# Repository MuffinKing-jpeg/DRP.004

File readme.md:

# DRP.004

Quack with the **new level**!

## Docs

- [Interactive BOM](./Docs/ibom.html)
- [Schematics](./Docs/DRP.004.pdf)
- [Production files](./production/)

## Changes in v3

- Completely new power design
  - 1.8v for MCU + LDR
  - ~5.5v for servo only
- Interface moved to one side.
- MOAR SILK!
- ENIG

## Changes in v4.2

- Switches moved to SMT parts
- Moved USB to same side as other user interfaces
- Changed battery connector to PH2.0
- Changed NTC thermistor to 0402
- Rerouted almost everything

## Changes in v4.3

- Threw to trash few useless resistors  
- Removed power-on by button
- Squished PCB to 27*42mm size  
- Fresh docs

## Changes in v4.4

- CI/CD
- TPS61022 -> TPS63020

## Issues to overcome

- [] Please works as v3

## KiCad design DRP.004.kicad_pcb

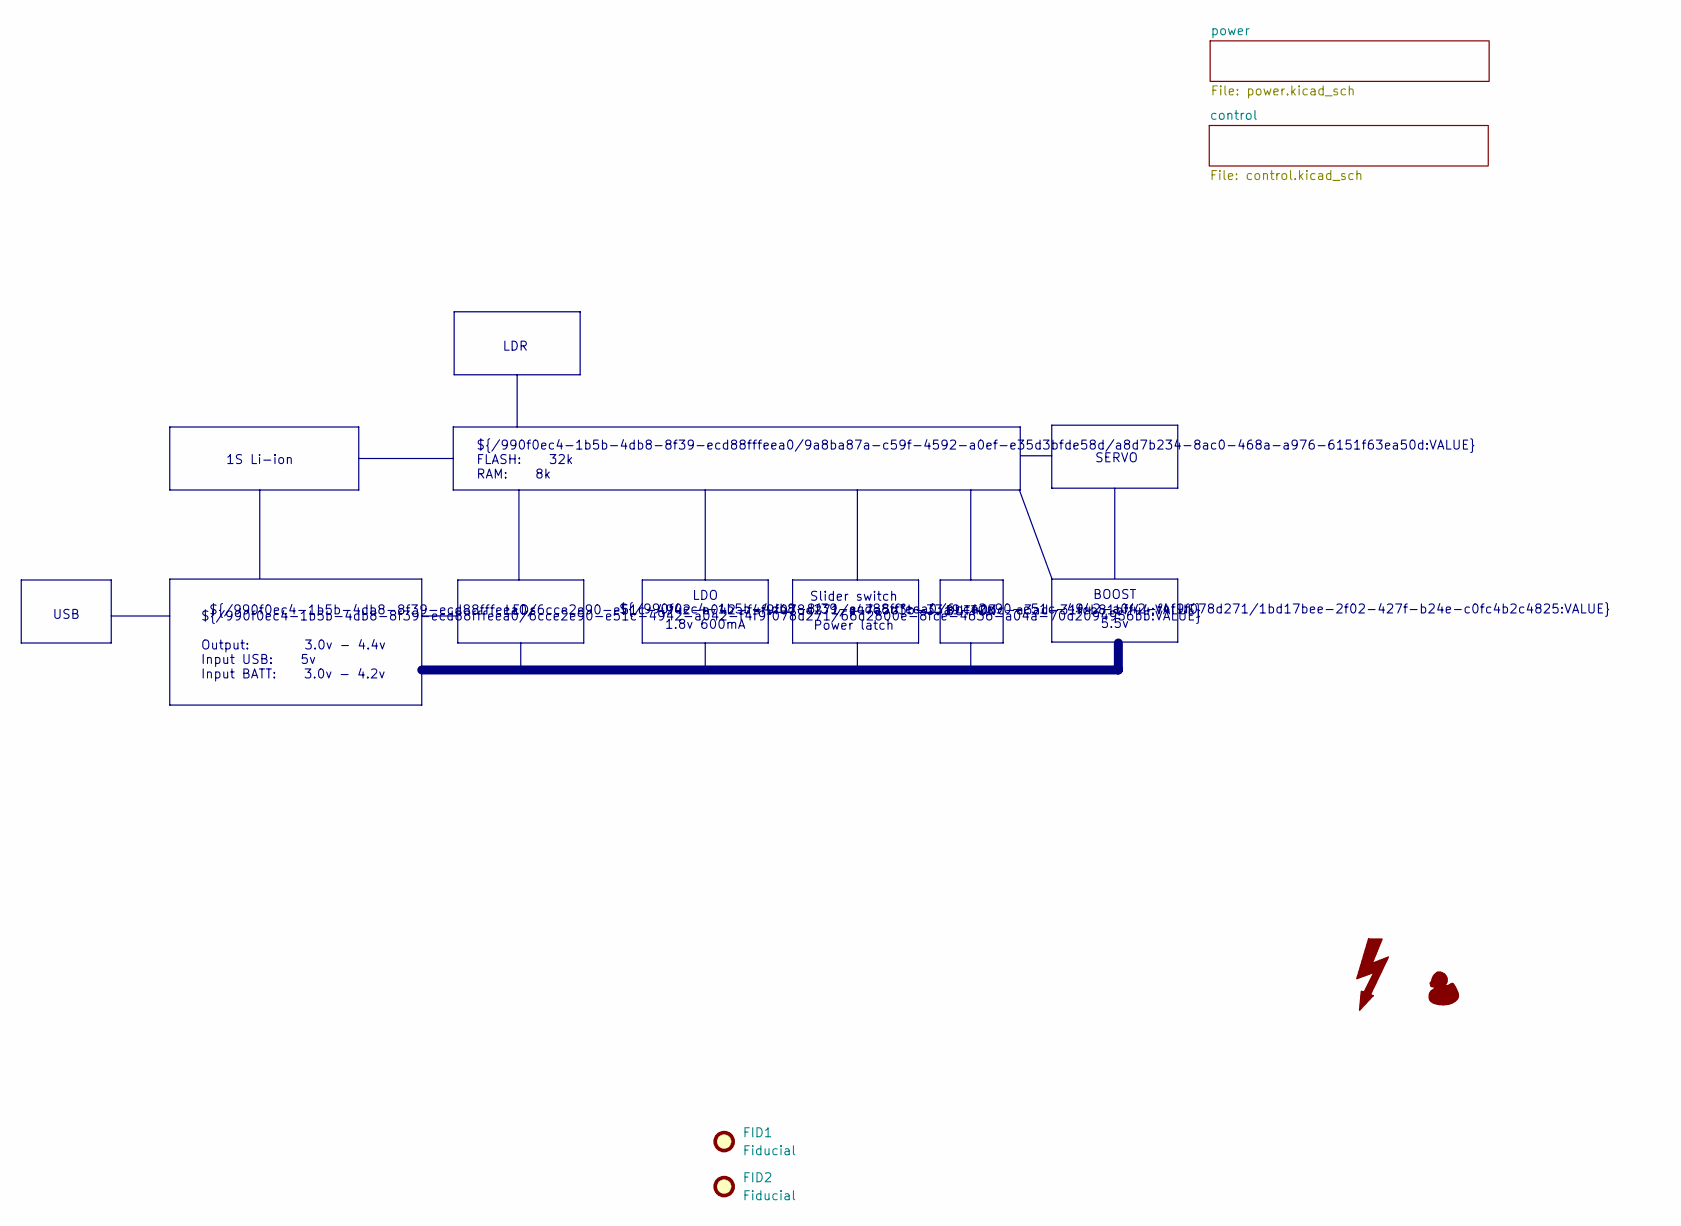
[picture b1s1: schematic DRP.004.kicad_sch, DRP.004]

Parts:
FID1, FID2: Fiducial; Fiducial_0.5mm_Mask1.5mm

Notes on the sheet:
Slider switch + Power latch
LEDs
SERVO
BOOST ${/990f0ec4-1b5b-4db8-8f39-ecd88fffeea0/6cce2e90-e51c-4942-a042-f4f9f078d271/1bd17bee-2f02-427f-b24e-c0fc4b2c4825:VALUE} 5.5v
USB
${/990f0ec4-1b5b-4db8-8f39-ecd88fffeea0/9a8ba87a-c59f-4592-a0ef-e35d3bfde58d/a8d7b234-8ac0-468a-a976-6151f63ea50d:VALUE} FLASH: 32k RAM: 8k
LDO ${/990f0ec4-1b5b-4db8-8f39-ecd88fffeea0/6cce2e90-e51c-4942-a042-f4f9f078d271/c47a5d3b-33a9-403c-a3ad-31fcb81bff44:VALUE} 1.8v 600mA
LDR
${/990f0ec4-1b5b-4db8-8f39-ecd88fffeea0/6cce2e90-e51c-4942-a042-f4f9f078d271/66d2800e-8fce-4636-a04a-70d2094956bb:VALUE} Output: 3.0v - 4.4v Input USB: 5v Input BATT: 3.0v - 4.2v
1S Li-ion
BUTTON

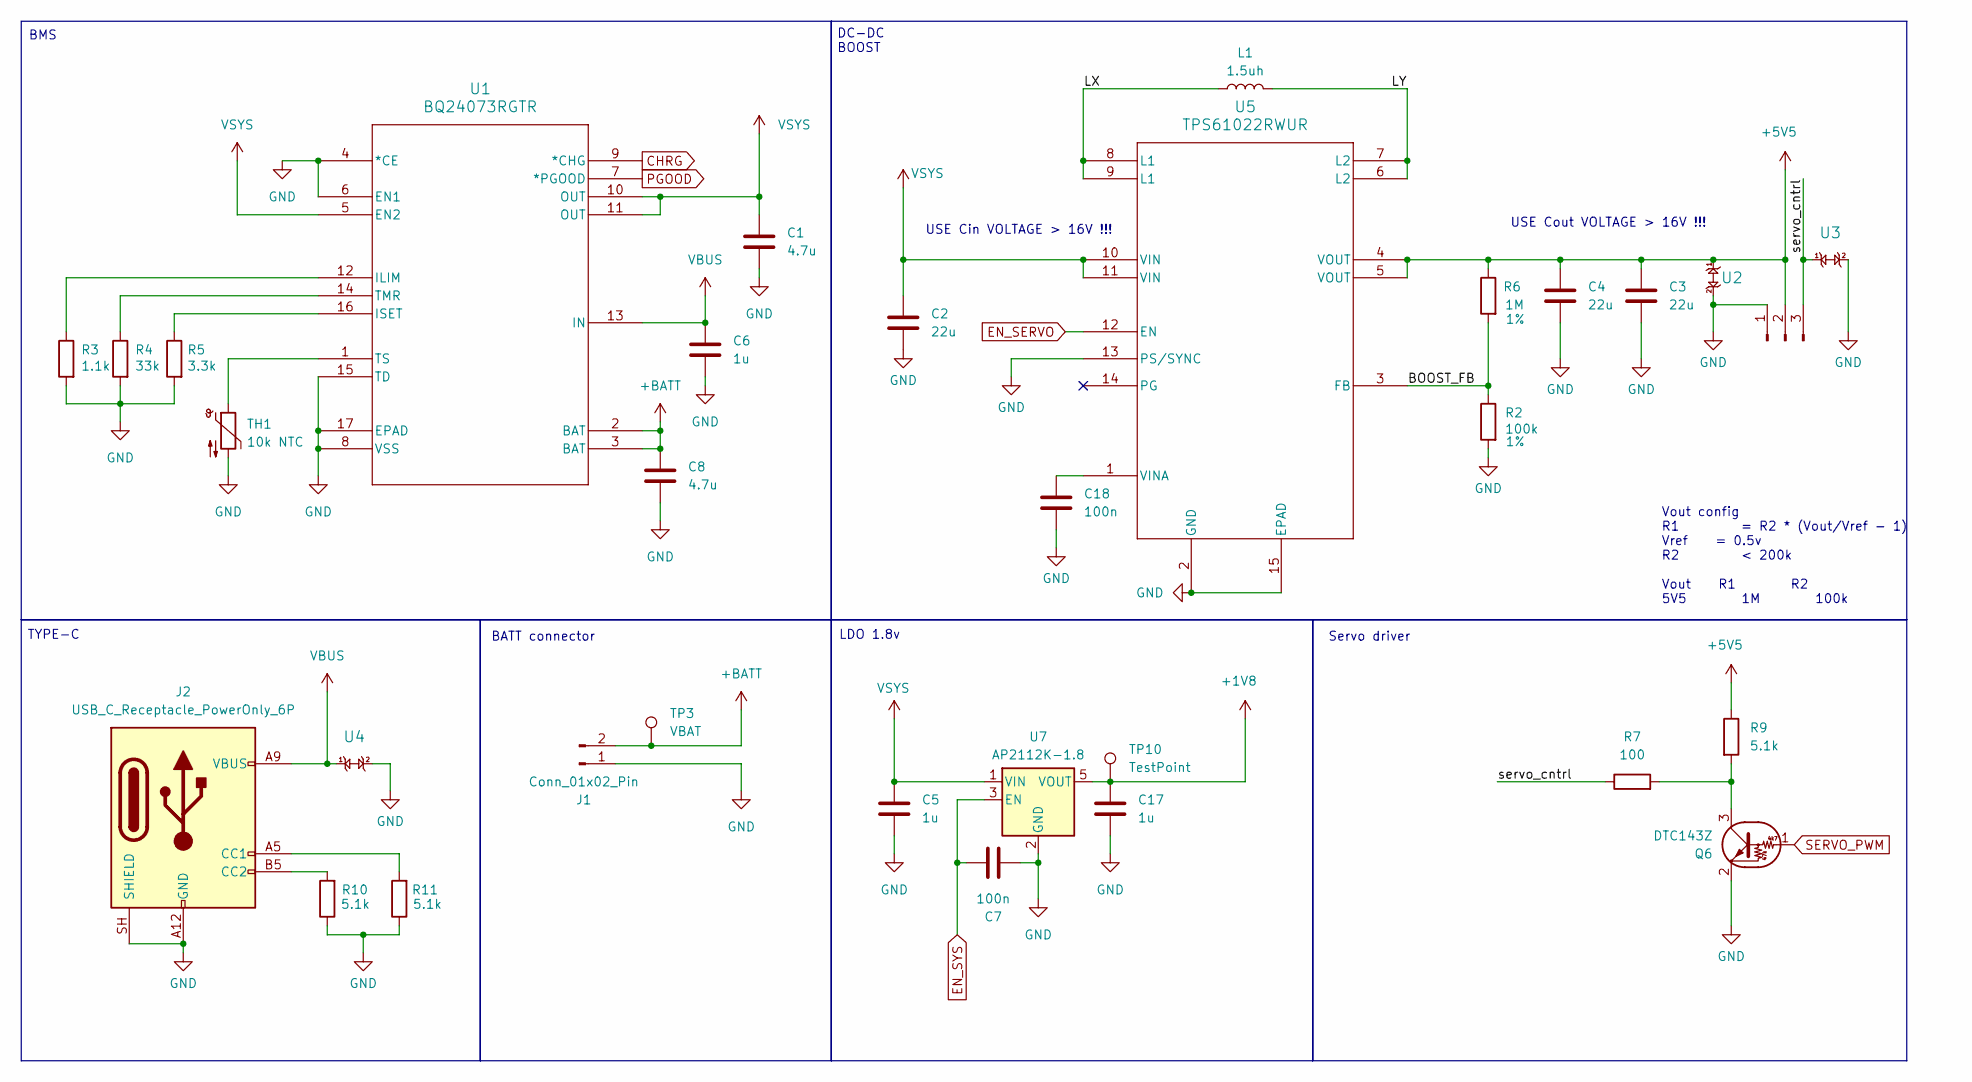
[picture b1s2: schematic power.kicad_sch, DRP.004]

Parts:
C1, C8: 4.7u; C_0603_1608Metric
C2, C3, C4: 22u; C_0805_2012Metric
C5, C6, C17: 1u; C_0603_1608Metric
C7, C18: 100n; C_0603_1608Metric
J1: Conn_01x02_Pin; JST_PH_S2B-PH-K_1x02_P2.00mm_Horizontal
J2: USB_C_Receptacle_PowerOnly_6P; USB_C_Receptacle_GCT_USB4125-xx-x-0190_6P_TopMnt_Horizontal
J3: Conn_01x03_Pin; PinHeader_1x03_P2.54mm_Horizontal
L1: 1.5uh; L_Changjiang_FTC322512S; LCSC C5179444
Q6: DTC143Z; SOT-523; LCSC C2828442
R2: 100k; R_0402_1005Metric; Tolerance 1%
R3: 1.1k; R_0603_1608Metric
R4: 33k; R_0603_1608Metric
R5: 3.3k; R_0603_1608Metric
R6: 1M; R_0402_1005Metric; Tolerance 1%
R7: 100; R_0603_1608Metric
R9, R10, R11: 5.1k; R_0603_1608Metric
TH1: 10k NTC; R_0402_1005Metric
TP3: VBAT; TestPoint_Pad_D1.0mm
TP10: TestPoint; TestPoint_Pad_D1.0mm
U1: BQ24073RGTR; RGT16; LCSC C15220
U2, U3, U4: TPD1E10B06DPYR; X1SON-2_L1.0-W0.6-P0.65-BI; LCSC C48260
U5: TPS61022RWUR; DSJ14_2P85X1P58; LCSC C15483
U7: AP2112K-1.8; SOT-23-5; LCSC C176944

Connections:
+1V8: C17.1, TP10.1 (1_1), U7.5 (VOUT); also elsewhere on the board
+5V5: C3.1, C4.1, J3.2, R6.1, R9.1, U2.1, U5.4 (VOUT), U5.5 (VOUT)
+BATT: C8.1, J1.2, TP3.1 (1_1), U1.2 (BAT), U1.3 (BAT); also elsewhere on the board
/power/BOOST_FB: R2.1, R6.2, U5.3 (FB)
/power/LX: L1.1, U5.8 (L1), U5.9 (L1)
/power/LY: L1.2, U5.6 (L2), U5.7 (L2)
/power/servo_cntrl: J3.3, R7.1, U3.1
CHRG: U1.9 (*CHG); also elsewhere on the board
EN_SERVO: U5.12 (EN); also elsewhere on the board
EN_SYS: C7.2, U7.3 (EN); also elsewhere on the board
GND: C1.2, C2.2, C3.2, C4.2, C5.2, C6.2, C7.1, C8.2, C17.2, C18.2, J1.1, J2.A12 (GND), J2.B12 (GND), J2.SH (SHIELD), J3.1, Q6.2 (E), R2.2, R3.2, R4.2, R5.2, R10.1, R11.1, TH1.2, U1.4 (*CE), U1.6 (EN1), U1.8 (VSS), U1.15 (TD), U1.17 (EPAD), U2.2, U3.2, U4.2, U5.2 (GND), U5.13 (PS/SYNC), U5.15 (EPAD), U7.2 (GND); also elsewhere on the board
unnamed: J2.A5 (CC1), R11.2
unnamed: J2.B5 (CC2), R10.2
unnamed: Q6.3 (C), R7.2, R9.2
unnamed: R3.1, U1.12 (ILIM)
unnamed: R5.1, U1.16 (ISET)
unnamed: R4.1, U1.14 (TMR)
unnamed: TH1.1, U1.1 (TS)
unnamed: C18.1, U5.1 (VINA)
PGOOD: U1.7 (*PGOOD); also elsewhere on the board
SERVO_PWM: Q6.1 (B); also elsewhere on the board
VBUS: C6.1, J2.A9 (VBUS), J2.B9 (VBUS), U1.13 (IN), U4.1
VSYS: C1.1, C2.1, C5.1, U1.5 (EN2), U1.10 (OUT), U1.11 (OUT), U5.10 (VIN), U5.11 (VIN), U7.1 (VIN); also elsewhere on the board

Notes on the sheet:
USE Cout VOLTAGE > 16V !!!
LDO 1.8v
DC-DC BOOST
TYPE-C
Servo driver
USE Cin VOLTAGE > 16V !!!
BMS
BATT connector
Vout config R1 = R2 * (Vout/Vref - 1) Vref = 0.5v R2 < 200k Vout R1 R2 5V5 1M 100k

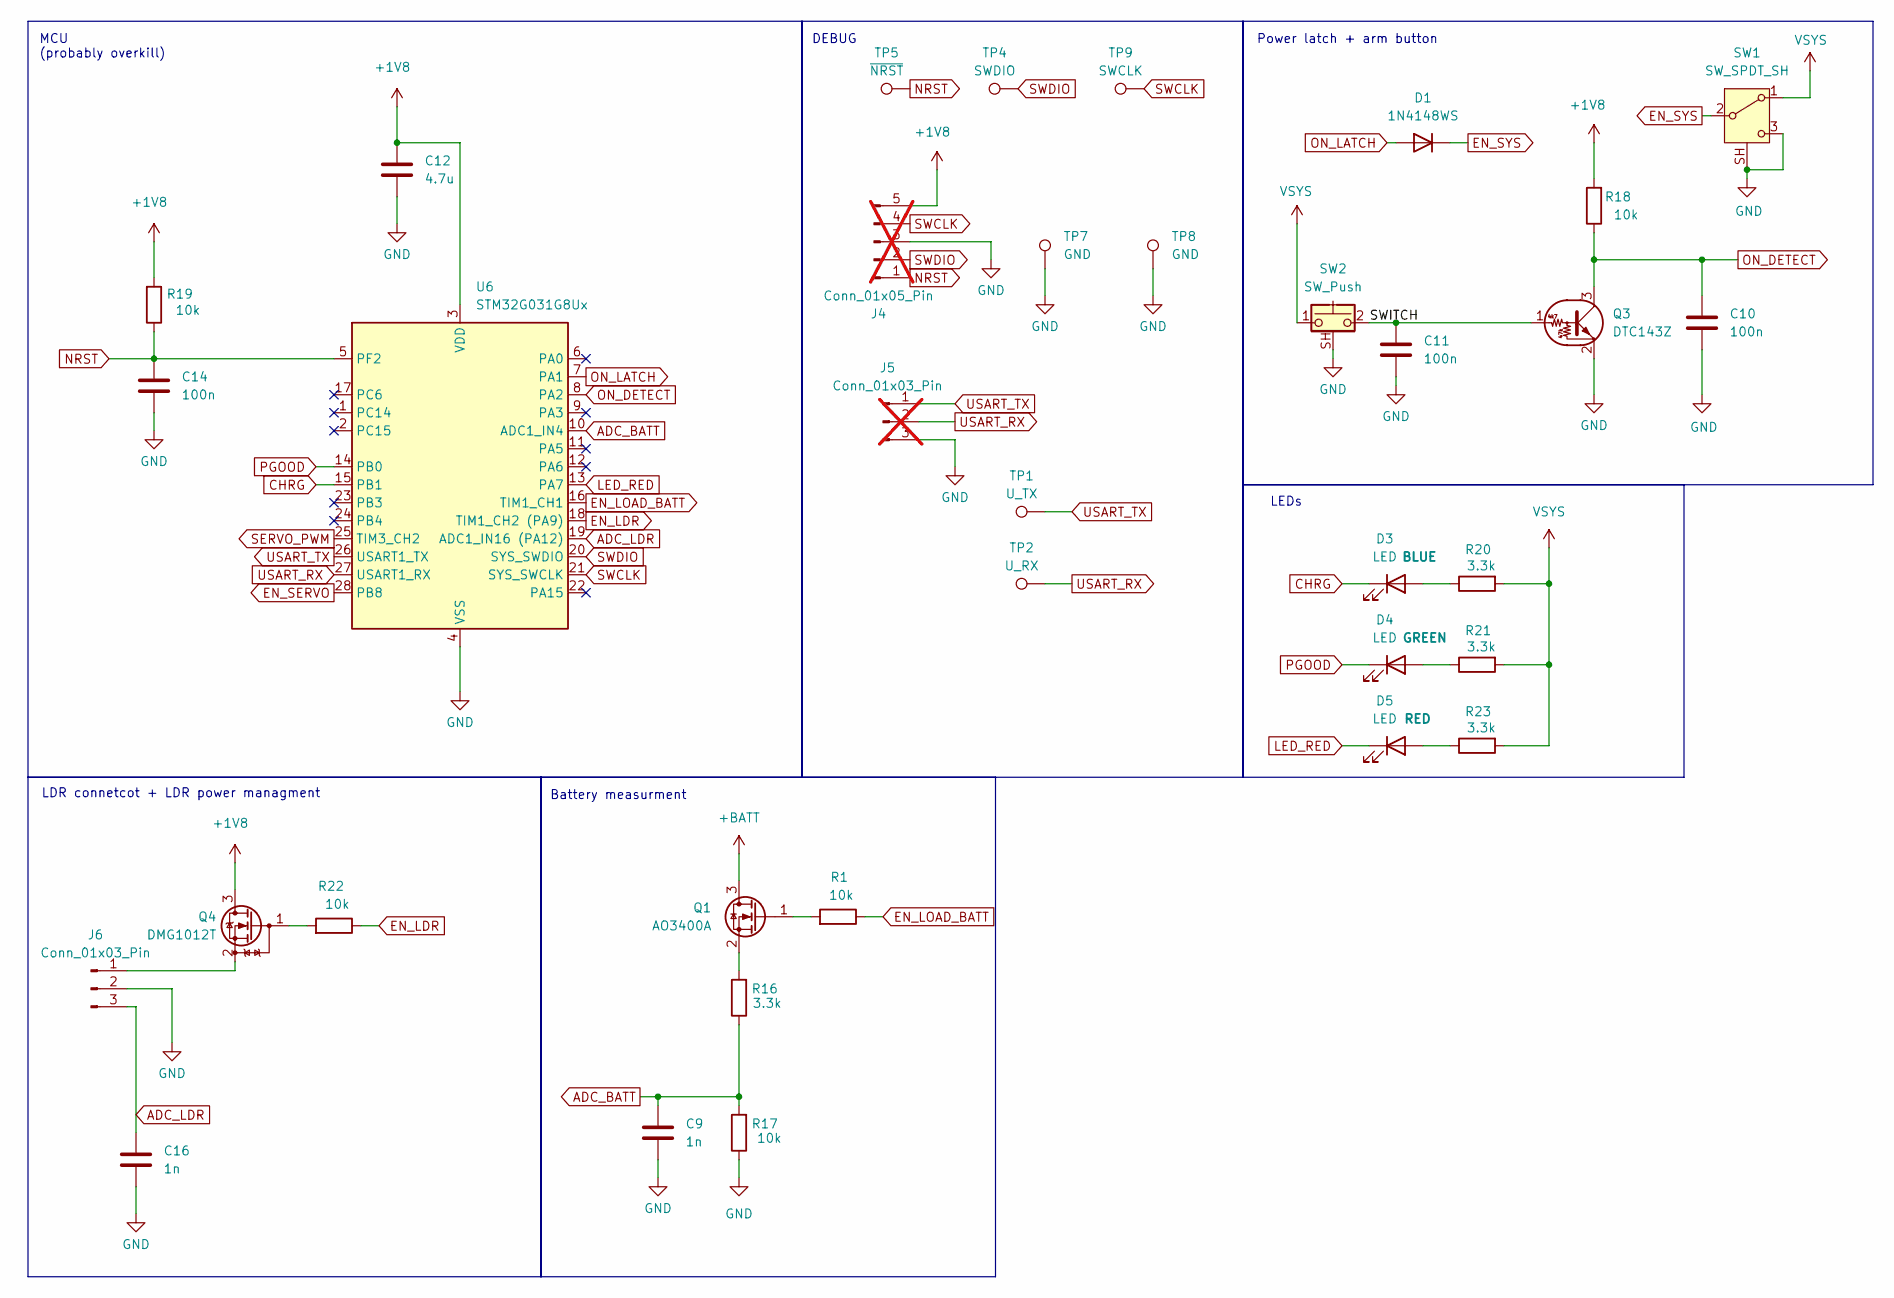
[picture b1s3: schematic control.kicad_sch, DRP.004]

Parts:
C9, C16: 1n; C_0603_1608Metric
C10, C11, C14: 100n; C_0603_1608Metric
C12: 4.7u; C_0603_1608Metric
D1: 1N4148WS; D_SOD-323; LCSC C6423741
D3, D4, D5: LED; LED_0805_2012Metric
J4: Conn_01x05_Pin; Molex_PicoBlade_53048-0510_1x05_P1.25mm_Horizontal; not fitted
J5: Conn_01x03_Pin; Molex_PicoBlade_53048-0310_1x03_P1.25mm_Horizontal; not fitted
J6: Conn_01x03_Pin; Molex_PicoBlade_53048-0310_1x03_P1.25mm_Horizontal
Q1: AO3400A; SOT-23
Q3: DTC143Z; SOT-523; LCSC C2828442
Q4: DMG1012T; SOT-523; LCSC C20512
R1, R17, R18, R19, R22: 10k; R_0603_1608Metric
R16, R20, R21, R23: 3.3k; R_0603_1608Metric
SW1: SW_SPDT_SH; MSK12C02; LCSC C109335
SW2: SW_Push; SW_Push_1P1T-MP_NO_Horizontal_Alps_SKRTLAE010; LCSC C398057
TP1: U_TX; TestPoint_Pad_D1.0mm
TP2: U_RX; TestPoint_Pad_D1.0mm
TP4: SWDIO; TestPoint_Pad_D1.0mm
TP5: ~{NRST}; TestPoint_Pad_D1.0mm
TP7, TP8: GND; TestPoint_Pad_D1.0mm
TP9: SWCLK; TestPoint_Pad_D1.0mm
U6: STM32G031G8Ux; QFN-28_4x4mm_P0.5mm; LCSC C432211

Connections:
+1V8: C12.1, J4.5, Q4.3 (D), R18.2, R19.2, U6.3 (VDD); also elsewhere on the board
+BATT: Q1.3 (D); also elsewhere on the board
/control/SWITCH: C11.1, Q3.1 (B), SW2.2
ADC_BATT: C9.1, R16.1, R17.2, U6.10 (ADC1_IN4)
ADC_LDR: C16.1, J6.3, U6.19 (ADC1_IN16 (PA12))
CHRG: D3.1 (K), U6.15 (PB1); also elsewhere on the board
EN_LDR: R22.1, U6.18 (TIM1_CH2 (PA9))
EN_LOAD_BATT: R1.1, U6.16 (TIM1_CH1)
EN_SERVO: U6.28 (PB8); also elsewhere on the board
EN_SYS: D1.1 (K), SW1.2 (B); also elsewhere on the board
GND: C9.2, C10.2, C11.2, C12.2, C14.2, C16.2, J4.3, J5.3, J6.2, Q3.2 (E), R17.1, SW1.3 (C), SW1.SH (Shield), SW2.SH (B), TP7.1 (1_1), TP8.1 (1_1), U6.4 (VSS); also elsewhere on the board
LED_RED: D5.1 (K), U6.13 (PA7)
NRST: C14.1, J4.1, R19.1, TP5.1 (1_1), U6.5 (PF2)
unnamed: D3.2 (A), R20.1
unnamed: D4.2 (A), R21.1
unnamed: D5.2 (A), R23.1
unnamed: J6.1, Q4.2 (S)
unnamed: Q1.1 (G), R1.2
unnamed: Q1.2 (S), R16.2
unnamed: Q4.1 (G), R22.2
ON_DETECT: C10.1, Q3.3 (C), R18.1, U6.8 (PA2)
ON_LATCH: D1.2 (A), U6.7 (PA1)
PGOOD: D4.1 (K), U6.14 (PB0); also elsewhere on the board
SERVO_PWM: U6.25 (TIM3_CH2); also elsewhere on the board
SWCLK: J4.4, TP9.1 (1_1), U6.21 (SYS_SWCLK)
SWDIO: J4.2, TP4.1 (1_1), U6.20 (SYS_SWDIO)
USART_RX: J5.2, TP2.1 (1_1), U6.27 (USART1_RX)
USART_TX: J5.1, TP1.1 (1_1), U6.26 (USART1_TX)
VSYS: R20.2, R21.2, R23.2, SW1.1 (A), SW2.1; also elsewhere on the board

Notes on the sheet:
MCU (probably overkill)
DEBUG
LEDs
LDR connetcot + LDR power managment
Power latch + arm button
Battery measurment

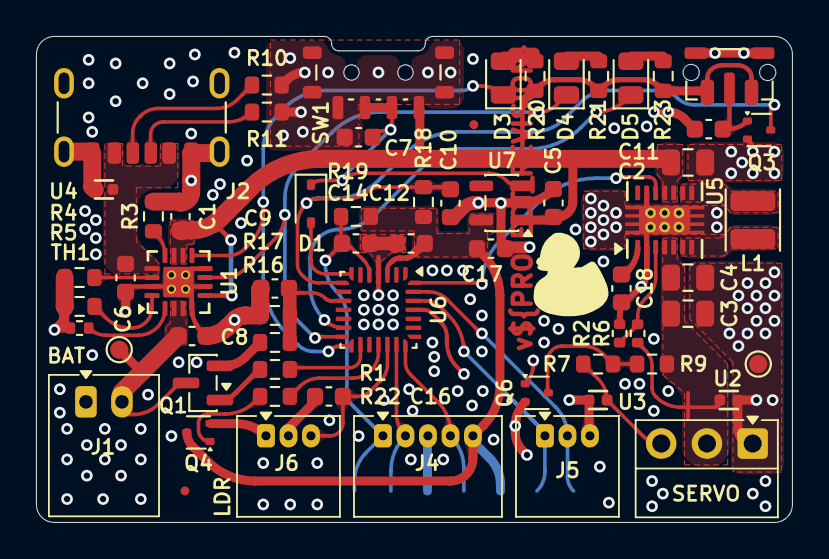
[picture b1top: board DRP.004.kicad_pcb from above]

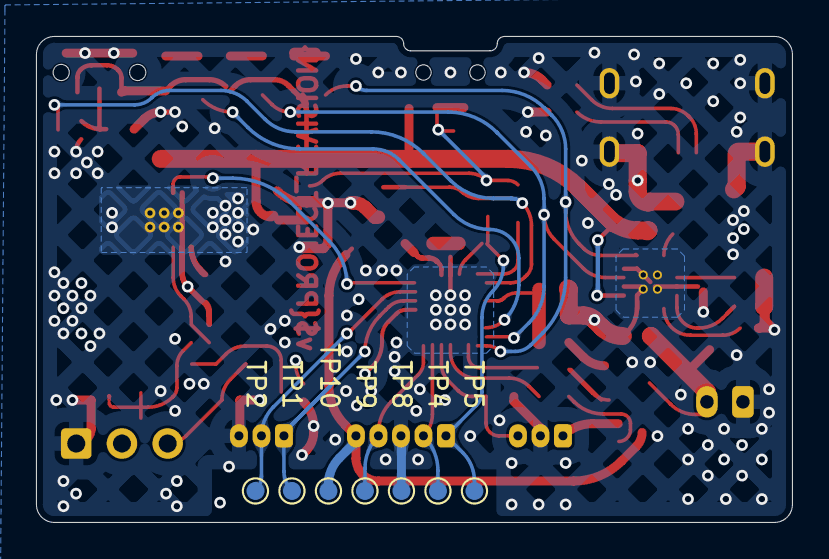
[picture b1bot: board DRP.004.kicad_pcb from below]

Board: 4 copper layers, 42.0 x 27.0 mm, 70 parts (7 on the bottom side), 43 nets.

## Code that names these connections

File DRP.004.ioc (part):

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Mcu.Name=STM32G031G(4-6-8)Ux
Mcu.Package=UFQFPN28
Mcu.UserName=STM32G031G8Ux
PA0.GPIOParameters=GPIO_Label
PA0.GPIO_Label=MODE_SW
PA0.Signal=GPIO_Output
PA1.GPIOParameters=GPIO_Label
PA1.GPIO_Label=LOAD_BATT
PA1.Signal=GPIO_Output
PA11\ [PA9].GPIOParameters=GPIO_Label
PA11\ [PA9].GPIO_Label=PMIC_CHRG
PA11\ [PA9].Signal=GPIO_Input
PA13.Mode=Serial_Wire
PA13.Signal=SYS_SWDIO
PA14-BOOT0.Mode=Serial_Wire
PA14-BOOT0.Signal=SYS_SWCLK
PA2.GPIOParameters=GPIO_Label
PA2.GPIO_Label=ADC_BATT
PA2.Mode=IN2
PA2.Signal=ADC1_IN2
PA3.GPIOParameters=GPIO_Label
PA3.GPIO_Label=ON_LATCH
PA3.Signal=GPIO_Output
PA4.GPIOParameters=GPIO_Label
PA4.GPIO_Label=WAKEUP
PA4.Mode=SYS_WakeUp1
PA4.Signal=SYS_WKUP2
PA5.GPIOParameters=GPIO_Label
PA5.GPIO_Label=HID_LED
PA5.Signal=S_TIM2_CH1_ETR
PA7.GPIOParameters=GPIO_Label
PA7.GPIO_Label=ADC_LDR
PA7.Mode=IN7
PA7.Signal=ADC1_IN7
PB1.GPIOParameters=GPIO_Label
PB1.GPIO_Label=LDR_ON
PB1.Signal=GPIO_Output
PB6.Signal=USART1_TX
PB7.Signal=USART1_RX
PB8.GPIOParameters=GPIO_Label
PB8.GPIO_Label=PWM_SERVO
PB8.Signal=S_TIM16_CH1
PC6.GPIOParameters=GPIO_Label
PC6.GPIO_Label=PMIC_PGOOD
PC6.Signal=GPIO_Input
RCC.HSE_VALUE=8000000
RCC.SYSCLKFreq_VALUE=16000000
board=custom

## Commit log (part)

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2025-04-05 Init commit
2025-04-05 Updated readme Updated ibom
2025-04-06 v1 Revision - Better routing - Added testpoints - DUCK - Tweaked drawings
2025-04-08 v2 Rev
2025-04-09 Updated paste layer
2025-04-09 Removed C5 Improved layout
2025-04-09 Return of the duck!
2025-04-09 Made prettier look
2025-04-10 Some cleanup
2025-04-19 Beautify placements (R20 R21 R23)
2025-04-20 Increased openings under PMICs
2025-05-06 Enabled project specific libs
2025-05-06 Added lib config
2025-05-06 Updated libs (again)
2025-05-06 Updated DOCS
2025-05-07 Buffed MOSFETs - Changed Q1,Q2 to AO3400 - Changed Q4 to DMG1012T
2025-05-07 Uodated production files
2025-05-31 Adjusted stencil for custom jig
2025-05-31 Updated renders
2025-07-19 Added list of issues to tweak in v3
2025-09-10 Removed PART folder
2025-09-10 Added PARTS as submodule
2025-09-15 Rough placment of components for v3
2025-09-15 Routed v3
2025-09-16 Finished v3
2025-09-16 Moved servo logic to 5v
2025-09-17 Removed cache
2025-09-17 Added stencil outline
2025-09-17 Expanded documentation
2025-09-18 Updated schematics. Calculated inductor values
2025-09-19 Prepeared production files
2025-09-19 Updated iBom
2025-09-21 Cleaned up libs
2025-09-21 Updated footprints
2025-10-11 Added automated jobs
2025-10-11 Updated production data and docs
2025-10-18 Updated project jobset - Added generation of ibom - Updated production files
2025-10-18 Added theme config for pages
2025-12-14 V4 revision - Moved usb to HID side - Changed battery connector to ph2.0 with standard(ish) pinout - Better footprints for debug and ldr connectors - Changed switch from SK12D07 to MSK12C02 - Changed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
2025-12-28 v4.1 - Changed SW2 to SMT (with lower profile) - Widen annular ring of vias - Small changes in routing (due to wider vias)
2025-12-28 v4.2 Revision - Rerouting again - New SW2
2026-03-15 v4.3 - Smaller, faster, stronger (lol) - Removed few appendixes - Updated doc jobs set
2026-06-08 Updated files in KiCAD 10.0.3
2026-06-08 Updated release project to new flow
2026-06-08 Added completely vibecodded CI pipeline
2026-06-08 remove .history from tracking
2026-06-08 Fixed typo in CI
2026-06-08 Moar fixes to vibecoded slop
2026-06-08 MOOOOAR FIXES TO SLOP..AND RLY, HOW I SUPpOSED TO DEBUG CI JOBS WITH ACTIONS, WTF?
2026-06-08 Removed DRC due do some quirks while used in jobs
2026-06-08 Some black magic (probably) to fix segfaults
2026-06-08 More black magic (added .pdf file extension for export)
2026-06-08 Some more tweaks (i don't believe)
2026-06-09 Added generation of stencil outline to joblist
2026-06-09 Tweaked stencil outline. Probably, hopefully, theoretically fixed CI
2026-06-09 Some black magic with X server
2026-06-09 Damn, man, i'm probably gaslighted by Claude
2026-06-09 Maybe this would work, idk
2026-06-09 Perms hit me at the face
2026-06-09 Desperation on it's finest
2026-06-09 Github, please, make some kind of emulator for debugging actions.
2026-06-09 At this point i don't know what i'm doing
2026-06-09 Bruh.
2026-06-09 Just attempt to generate better logs
2026-06-09 ARGH.
2026-06-09 BLEGH
2026-06-09 I really hate github CI, i should move to gitlab
2026-06-09 Removed ERC. Removeed ||true from jobs
